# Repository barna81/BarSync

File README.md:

<picture><source media="(prefers-color-scheme: dark)" srcset="images/BarSync_logo_white.svg"><source media="(prefers-color-scheme: light)" srcset="images/BarSync_logo.svg"></picture>
<p align="right">
<b>MIDI Clock Bar Counter</b><br/>
<sub><i>-Always in Time.-</i></sub>
</p>
<br clear="left"/>

*[Deutsche Version](README.de.md)*

BarSync is an ESP32-based device that receives an incoming MIDI clock and
displays bar position, beat progress, tempo, and elapsed play time on a
128×64 OLED display.

## Status (as of 2026-09-22)

BarSync - Desktop version (this device) 
- Current firmware: 1.3.2  
Improvements: introduced a browser-based firmware flasher — firmware
can now be flashed straight from the browser (Chrome/Edge), no Arduino
IDE needed, see the "Flashing the Firmware" section below; no
functional firmware changes
- Firmware: 1.3.1  
    Improvements: SCROLL mode with a much clearer sense of motion (stripe
    pattern + marker halo), extended bar/playtime counter limits, grid
    counter/BPM detection now keep running seamlessly in the background,
    various button-combo bug fixes
- Firmware: 1.3.0  
    New features: Marker Editor (place your own markers on the bar grid), two grid display modes (CYCLE/SCROLL), End Bar (loop/stop/continue the count at a defined bar)
- Schematic, PCB layout (hardware rev. 1.2), and firmware finished and tested
- PCBs for self-assembly have arrived
- A matching 3D-printable enclosure is available here [`enclosure`](enclosure/)
- A solder-it-yourself kit is being considered, depending on interest

BarSync - Eurorack version (in development, not yet on GitHub)
- Code finished
- PCB layout finished and ordered
- Schematic and PCB layout to follow
- 3D-printable Eurorack frame is in development

*(Interested in the kit or the Eurorack version? Open an issue in this repo or get in touch.)*

---

## What is this?
Never miss the drop...

BarSync keeps you locked into your track's arrangement — live or in the studio. Know exactly where you stand in the bar count, so drops, breaks and builds never catch you off guard.

Since I couldn't find anything similar on the market or in the DIY scene, I built BarSync.
BarSync supports you during your live performance. During a show your hands are usually full, and it's easy to lose track of the timing. No more counting bars in your head to land the drop at the right moment: BarSync counts and visualizes the bars elapsed since a starting point you define yourself. That starting point can be the first MIDI clock signal from your sequencer, or you can reset it at any time with the reset button. This way you always know exactly which bar you're in. The visualization adapts to your needs (1-128 bars can be displayed).

## Features

- Bar/beat counter, synced to the incoming MIDI clock (24 PPQN)
- Grid progress bar (x1 to x128 bars) — overall area stays constant,
  tile size adapts accordingly
- Two grid display modes: CYCLE (repeating cycle) or SCROLL
  (continuous, with markers scrolling into view)
- Marker Editor: place your own markers on the bar grid (4 symbols) —
  for arrangement points, phrase starts, or band cues
- End Bar: automatically loop, stop, or continue the count at a
  defined bar — fixed, or at your last placed marker
- 5 selectable time signatures (2/4, 3/4, 4/4, 5/4, 7/8)
- Reset button: two stages (short = bar end, medium/hold = cycle end) — each independently configurable whether it also resets the elapsed play time (default: yes). Plus a standalone "SET 1.1" function (default custom-button role) to instantly re-anchor the beat pattern, either quantized (rounded to the nearest beat) or instant (raw tick) — selectable in the settings menu
- MIDI Monitor (Note/CC/PC/Pitch Bend log, MIDI clock and RUN/STOP graph) right on the device
- Nudge mode for manually compensating clock phase drift
- MIDI-Thru
- Standby (light sleep) on MIDI inactivity
- On-device settings menu (no app or software required)

## Operation

Quick overview — full guide in
[`docs/BarSync_Quickstart_EN.pdf`](docs/BarSync_Quickstart_EN.pdf):

| Button | Function |
|---|---|
| Custom button (short) | SET 1.1 (re-anchor beat pattern)* |
| Custom button (hold 1s) | Toggle MIDI Monitor** |
| Grid (short) | Change the number of bars shown in the grid (x1–x128) |
| Reset (short/medium) | Reset stage 1/2 |
| Custom button + Grid together | Toggle nudge mode |
| Hold Reset 1s at boot | Settings menu |

*Configurable in setup: custom button for cycling through the time signatures, or SET1.1 (default)  
**In the MIDI Monitor screen, the reset button clears the Note/CC log instead of triggering its normal reset function.

---

## Cool! How do I get one?

If you'd like to build the device yourself, see [LICENSE](LICENSE) — you'll find the corresponding firmware, schematic, and parts list here. I've also designed a PCB, whose layout is included as well. Since it's a fairly simple layout, you can also use perfboard or even a breadboard to build BarSync. Basic knowledge of the ESP32, a soldering iron, and general electronics will be helpful.

In short: the project is currently still in a full DIY stage. Depending on interest, I'm considering offering a BarSync kit. It would come with a 3D-printed enclosure, a PCB, and all the necessary electronic components ready to be assembled. All that would be left to do is soldering and flashing the ESP32.

## Building Your Own

- Full [`schematic`](hardware/kicad/BarSync/BarSync_schematic.pdf)  
- PCB layout, and Gerber files are in [`hardware/`](hardware/)  
- Full bill of materials: [`hardware/BarSync_BOM.en.md`](hardware/BarSync_BOM.en.md)  
- Electronic parts as a ready-made Reichelt cart: [reichelt.de/my/2391791](https://www.reichelt.de/my/2391791)  
- Assembly guide: [`hardware/BarSync_Aufbauanleitung.en.md`](hardware/BarSync_Aufbauanleitung.en.md)  
- 3D-printable enclosure available here: [`enclosure`](enclosure/)

## What´s inside?
First build with the new PCB!  

## Key Hardware

- ESP32 dev board (30-pin DOIT layout)
- SSD1309 OLED, 2.42", 128×64, SPI
- 3 buttons (custom, grid, reset)

## Flashing the Firmware

### 1. Web Flasher (recommended)

Right from your browser, no Arduino IDE, no driver install — works in Chrome or Edge (Windows/macOS/Linux):

**[barna81.github.io/BarSync/flash](https://barna81.github.io/BarSync/flash/)**

### 2. Manual Flashing (Arduino IDE)

For anyone who prefers to compile it themselves, or whose browser doesn't support the web flasher (e.g. Safari, Firefox). Detailed step-by-step instructions incl. USB driver install: see **Chapter 8 "Flash the Firmware"** in the [Assembly Guide](hardware/BarSync_Aufbauanleitung.en.md).

Short version:
1. Install the Arduino IDE, add ESP32 board support
2. Install libraries: [**"MIDI Library"**](https://github.com/FortySevenEffects/arduino_midi_library) (FortySevenEffects), [**"U8g2"**](https://github.com/olikraus/u8g2) (olikraus)
3. Open [`firmware/barsync.ino`](firmware/barsync.ino), select board "ESP32 Dev Module", upload

## License

This project is licensed under **CC BY-NC-SA 4.0** — see [LICENSE](LICENSE).
Free to use, modify, and share for **non-commercial** purposes, with
attribution and share-alike terms. For commercial use, please get in touch.

---

*[Deutsche Version](README.de.md)*

*Built with a lot of debugging, deep MIDI timing analysis, and an
occasional detour into building a Space Invaders clone.*

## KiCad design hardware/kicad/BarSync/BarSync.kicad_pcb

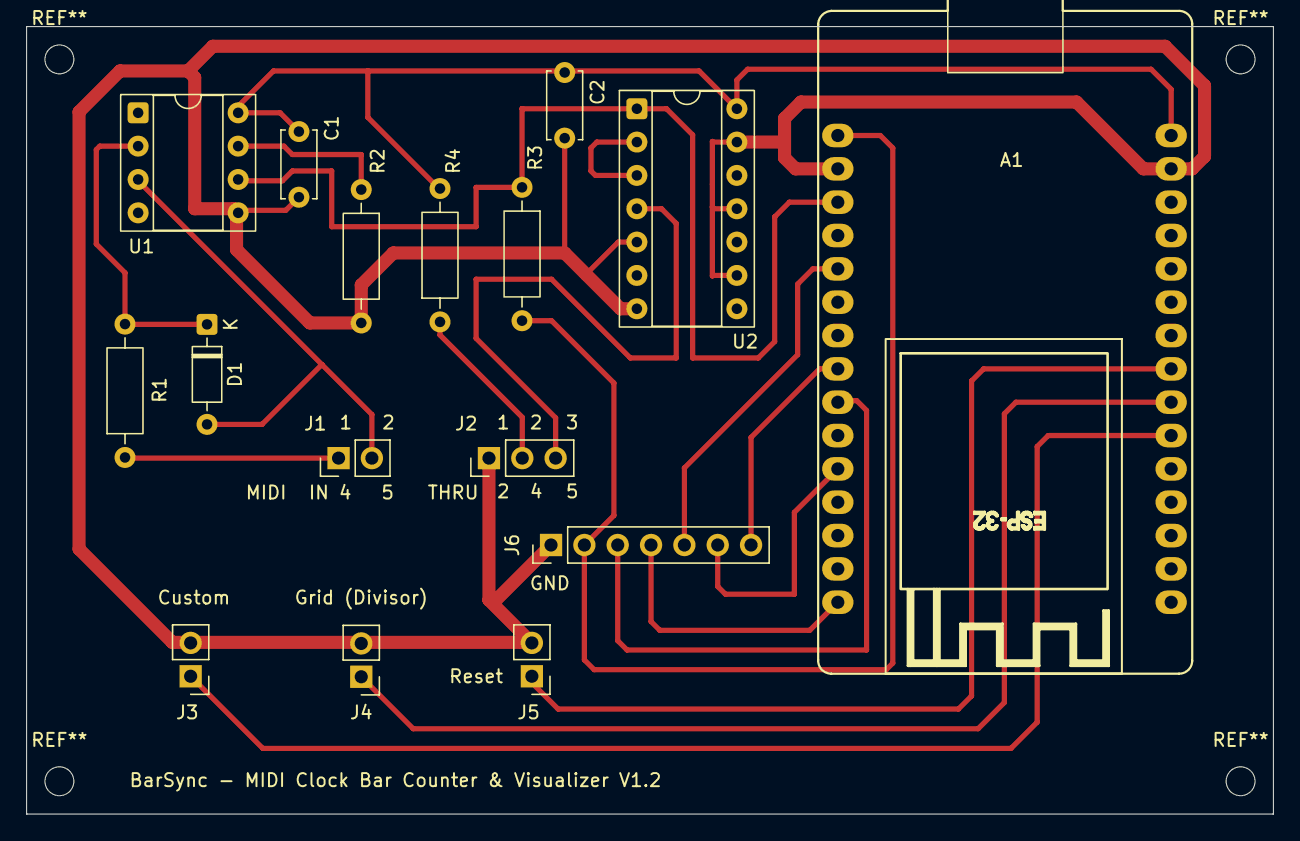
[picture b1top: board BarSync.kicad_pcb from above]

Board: 2 copper layers, 95.0 x 60.0 mm, 16 parts (0 on the bottom side), 19 nets.

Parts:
A1: ESP32_DevKit_V1_DOIT_30GPIOs; DOIT_ESP32_DEVKIT_30Pins
C1, C2: 100n; C_Disc_D5.0mm_W2.5mm_P5.00mm
D1: 1N4148; D_DO-35_SOD27_P7.62mm_Horizontal
J1: MIDI; PinHeader_1x02_P2.54mm_Vertical
J2: THRU; PinHeader_1x03_P2.54mm_Vertical
J3: Custom; PinHeader_1x02_P2.54mm_Vertical
J4: Grid (Divisor); PinHeader_1x02_P2.54mm_Vertical
J5: Reset; PinHeader_1x02_P2.54mm_Vertical
J6: Connector; PinHeader_1x07_P2.54mm_Vertical
R1, R3, R4: 220; R_Axial_DIN0207_L6.3mm_D2.5mm_P10.16mm_Horizontal
R2: 4k7; R_Axial_DIN0207_L6.3mm_D2.5mm_P10.16mm_Horizontal
U1: 6N139; DIP-8_W7.62mm_Socket
U2: SN7406N; DIP-14_W7.62mm_Socket

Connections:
GND: A1.2 (GND), A1.29 (GND), C1.2, C2.2, J2.1, J3.2, J4.2, J5.2, J6.1 (PIN_1), R2.2, U1.5, U2.5, U2.7, U2.9, U2.11, U2.13
unnamed: A1.1 (3.3V), J6.2 (PIN_2), R3.2
unnamed: A1.21 (ADC1_CH4/D32), J3.1
unnamed: A1.22 (ADC1_CH5/D33), J4.1
unnamed: A1.5 (D4/ADC2_CH0), J6.5 (PIN_5)
unnamed: A1.8 (D5), J6.7 (PIN_7)
unnamed: A1.3 (D15/ADC2_CH3), R3.1, U1.6, U2.1
unnamed: A1.9 (D18), J6.3 (PIN_3)
unnamed: A1.11 (D21/SDA), J6.6 (PIN_6)
unnamed: A1.15 (D23), J6.4 (PIN_4)
unnamed: A1.23 (DAC1/ADC2_CH8/D25), J5.1
unnamed: A1.30 (VIN(+5V)), C1.1, C2.1, R4.2, U1.8, U2.14
unnamed: D1.2 (A), J1.2, U1.3
unnamed: D1.1 (K), R1.2, U1.2
unnamed: J1.1, R1.1
unnamed: J2.2, R4.1
unnamed: J2.3, U2.4
unnamed: R2.1, U1.7
unnamed: U2.2, U2.3
